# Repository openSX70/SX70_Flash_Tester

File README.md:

# SX70_Flash_Tester
As described in the SX70 Repair Manual

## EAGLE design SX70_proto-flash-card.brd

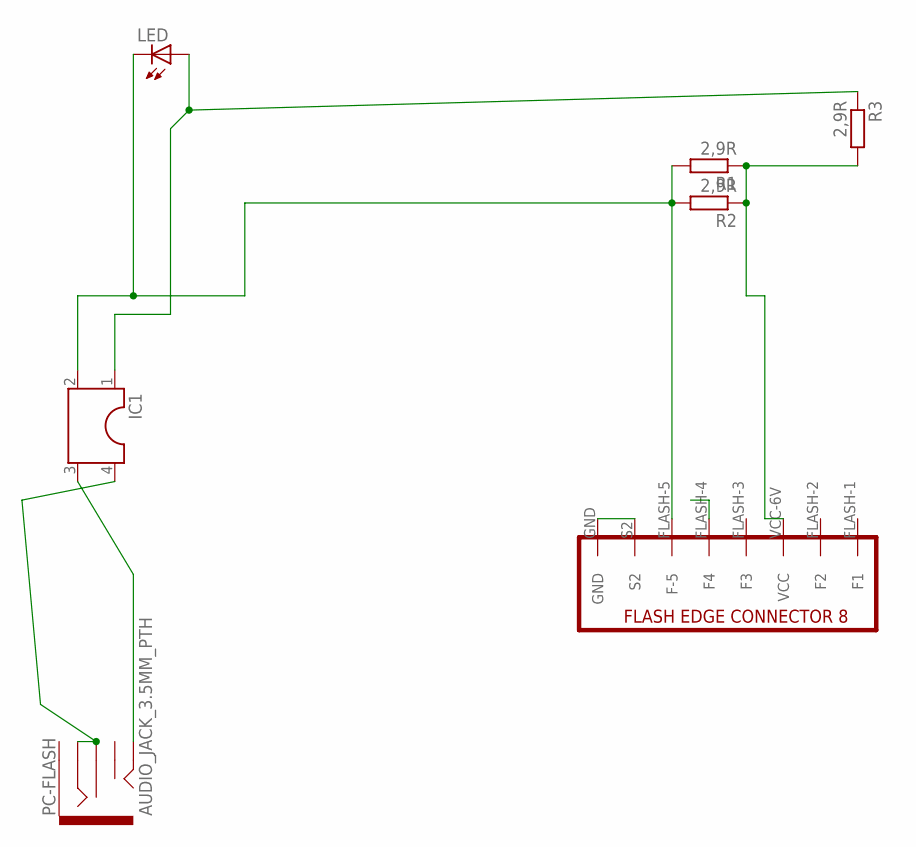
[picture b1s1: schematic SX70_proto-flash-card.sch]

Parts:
FLASH-TESTER: SX70-FLASH-EDGE8-MALE; SX70-FLASH-EDGE8
IC1: DIL4; DIL04
LED: LED3MM
PC-FLASH: AUDIO_JACK_3.5MM_PTH; AUDIO-JACK
R1, R2, R3: 2,9R; 0204/7

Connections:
unnamed: FLASH-TESTER.GND, FLASH-TESTER.S2
unnamed: FLASH-TESTER.FLASH-5 (F-5), IC1.2, LED.K (C), R1.2, R2.2
unnamed: FLASH-TESTER.VCC-6V (VCC), R1.1, R2.1, R3.2
unnamed: IC1.1, LED.A, R3.1
unnamed: IC1.4, PC-FLASH.RING, PC-FLASH.RSH
unnamed: IC1.3, PC-FLASH.TIP

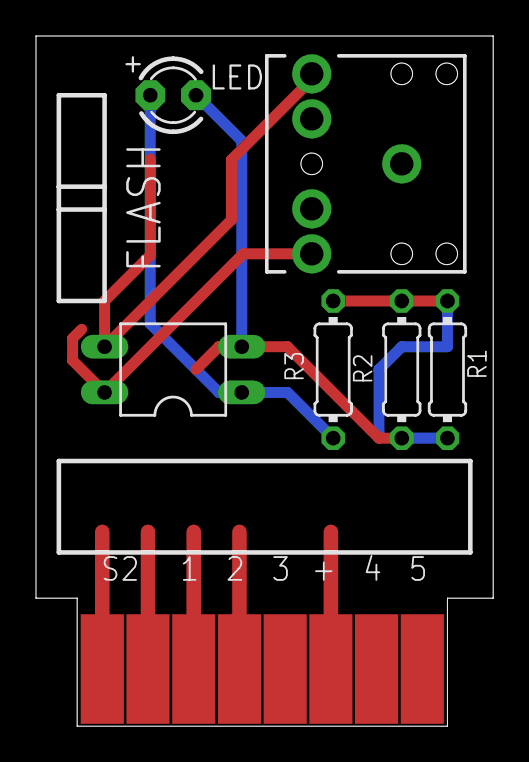
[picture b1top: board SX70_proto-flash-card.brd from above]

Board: 2 copper layers, 25.4 x 38.3 mm, 7 parts (0 on the bottom side), 6 nets.

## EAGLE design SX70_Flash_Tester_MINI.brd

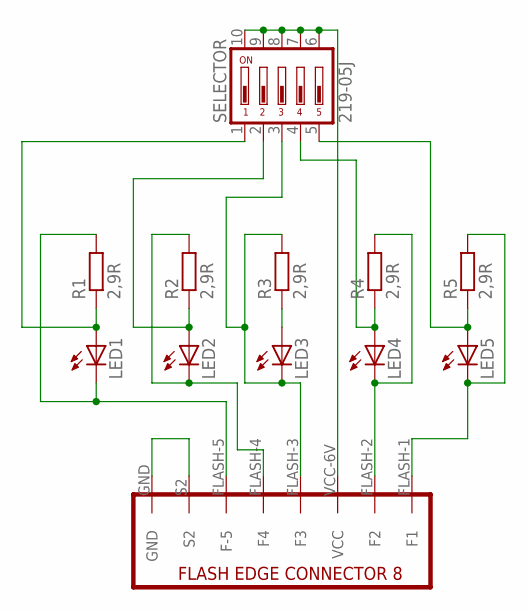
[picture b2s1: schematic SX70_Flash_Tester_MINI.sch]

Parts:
FLASH_TESTER: SX70-FLASH-EDGE8-MALE; SX70-FLASH-EDGE8
LED1, LED2, LED3, LED4, LED5: LEDCHIPLED_0805; CHIPLED_0805
R1, R2, R3, R4, R5: 2,9R; M0805
SELECTOR: 219-05J; CTS-219-05J

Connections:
unnamed: LED1.A, R1.1, SELECTOR.1
unnamed: LED2.A, R2.1, SELECTOR.2
unnamed: LED3.A, R3.1
unnamed: FLASH_TESTER.VCC-6V (VCC), SELECTOR.6, SELECTOR.7, SELECTOR.8, SELECTOR.9, SELECTOR.10
unnamed: LED5.A, R5.1, SELECTOR.5
unnamed: FLASH_TESTER.FLASH-1 (F1), LED5.C, R5.2
unnamed: FLASH_TESTER.FLASH-2 (F2), LED4.C, R4.2
unnamed: FLASH_TESTER.FLASH-3 (F3), LED3.C, R3.2, SELECTOR.3
unnamed: FLASH_TESTER.FLASH-4 (F4), LED2.C, R2.2
unnamed: FLASH_TESTER.FLASH-5 (F-5), LED1.C, R1.2
unnamed: FLASH_TESTER.GND, FLASH_TESTER.S2
unnamed: LED4.A, R4.1, SELECTOR.4

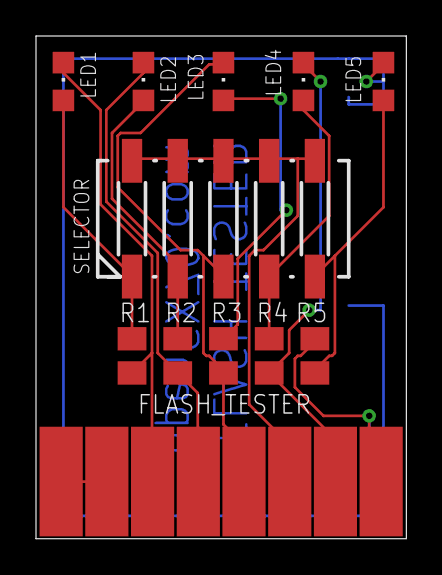
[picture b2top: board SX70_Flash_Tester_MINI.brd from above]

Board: 2 copper layers, 20.6 x 27.9 mm, 12 parts (0 on the bottom side), 12 nets.

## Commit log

2017-11-29 Initial commit.
    Tester as described in Repair Manual
2017-11-29 Advance in the PCB
2017-11-30 new SCH
2017-11-30 not sure what I am doing
2017-11-30 changed pcb placement
2017-11-30 I have designed and ordered at OSHPARK a "mini" flash tester.
2017-11-30 Added a "mini tester" and finished the through hole tester. Ordered both (different orders) from OSHPark
2019-09-26 new flash adapter

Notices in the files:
parts and their libraries:
SparkFun-Connectors: Licensing: Creative Commons ShareAlike 4.0 International - https://creativecommons.org/licenses/by-sa/4.0
